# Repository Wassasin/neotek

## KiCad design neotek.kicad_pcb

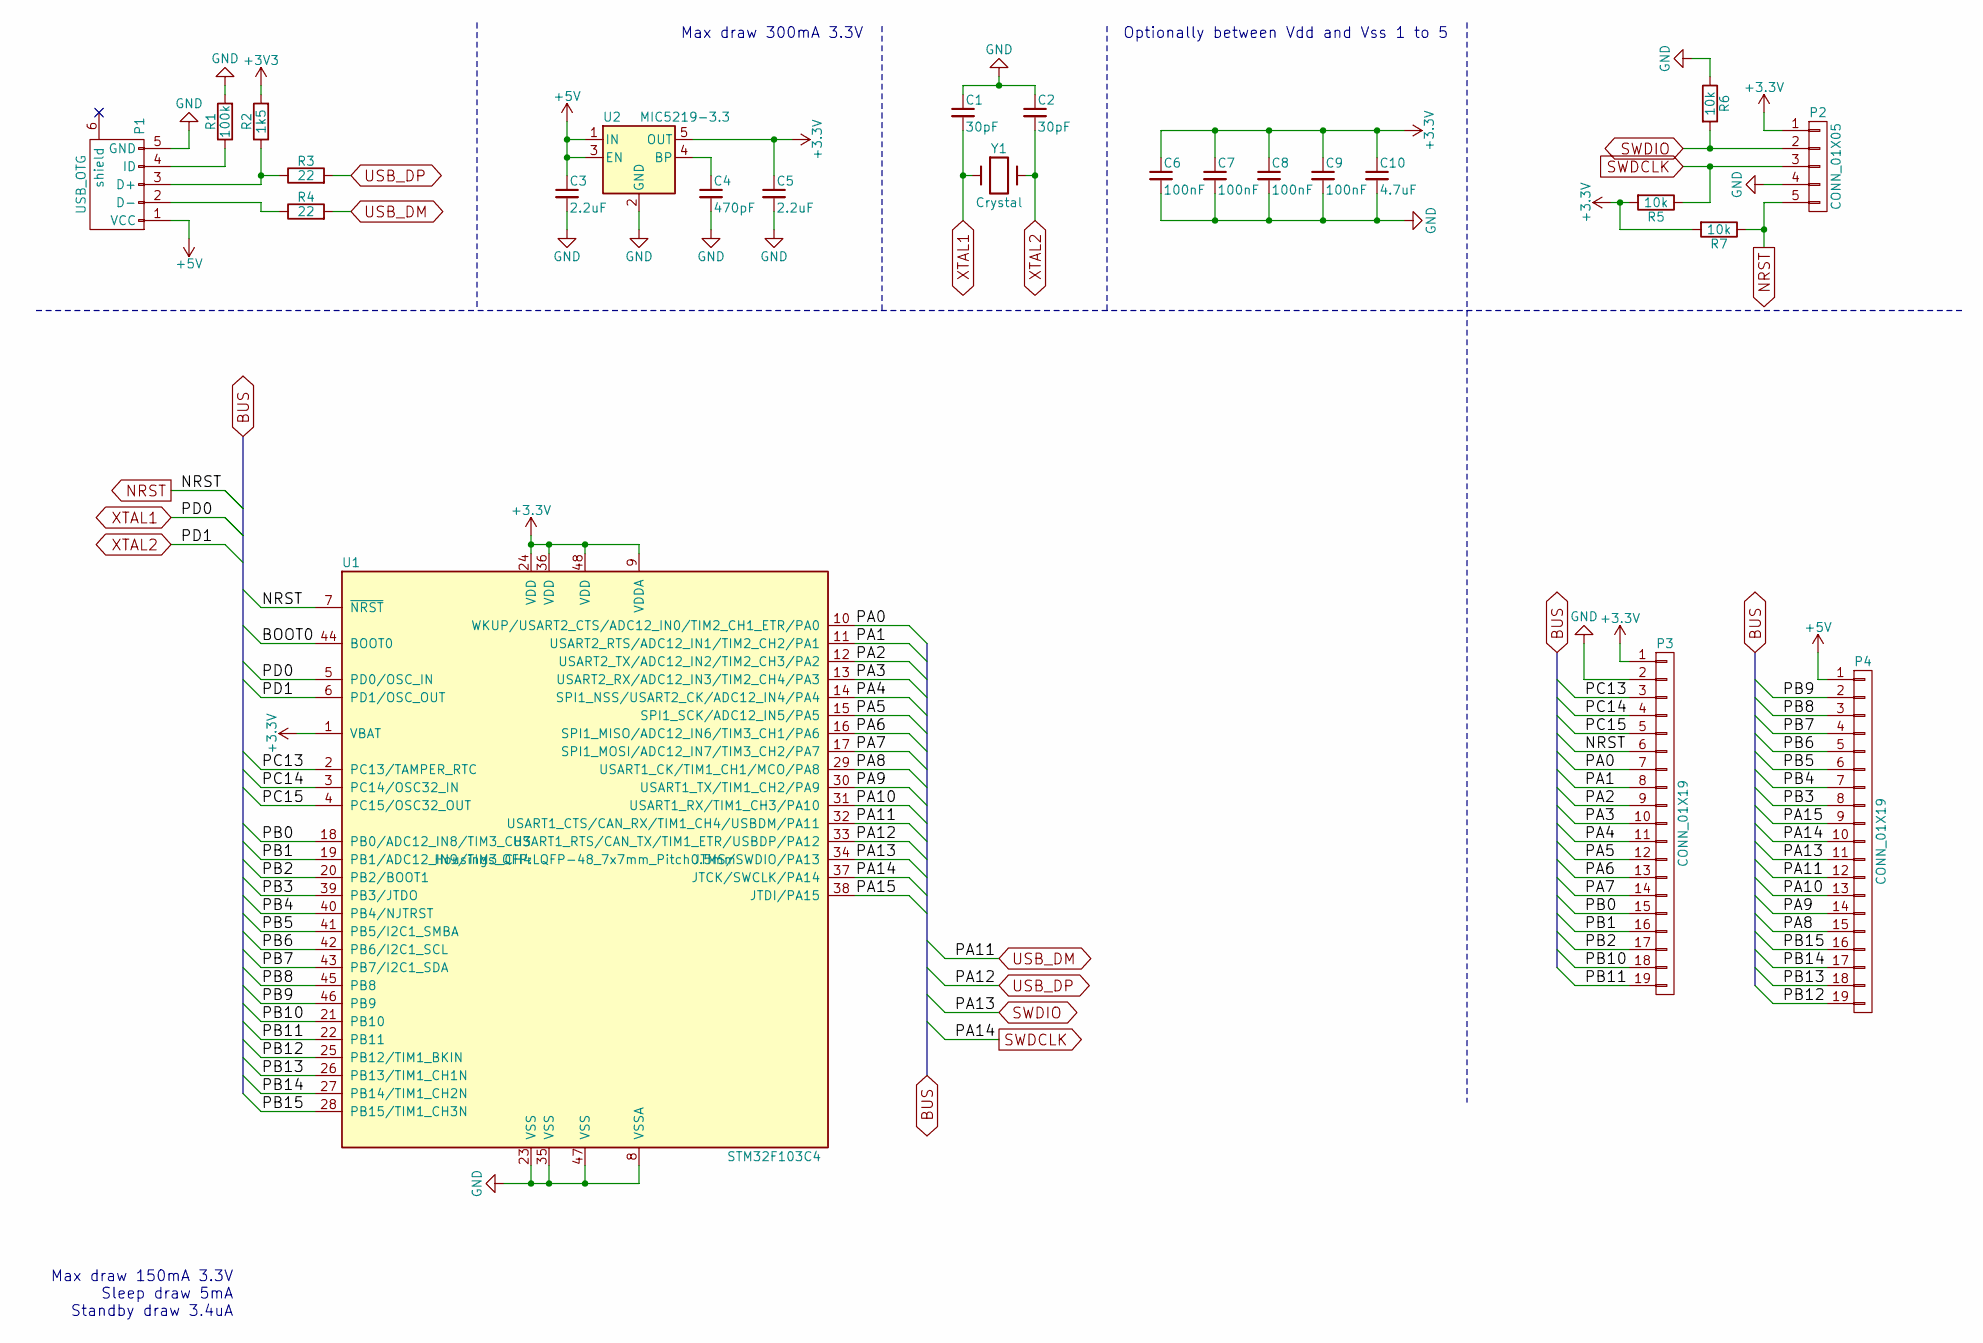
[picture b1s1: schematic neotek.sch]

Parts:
C1, C2: 30pF; C_0603_HandSoldering
C3, C5: 2.2uF; C_0603_HandSoldering
C4: 470pF; C_0603_HandSoldering
C6, C7, C8, C9: 100nF; C_0603_HandSoldering
C10: 4.7uF; C_0603_HandSoldering
P1: USB_OTG; USB_Micro-B_10103594-0001LF
P2: CONN_01X05; Hirose_DF13-05P-1.25DS_05x1.25mm_Angled
P3, P4: CONN_01X19; Pin_Header_Straight_1x19
R1: 100k; R_0603_HandSoldering
R2: 1k5; R_0603_HandSoldering
R3, R4: 22; R_0603_HandSoldering
R5, R6, R7: 10k; R_0603_HandSoldering
U1: STM32F103C4; LQFP-48_7x7mm_Pitch0.5mm
U2: MIC5219-3.3; SOT-23-5
Y1: Crystal; Crystal_HC49-SD_SMD

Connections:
+5V: C3.1, P1.1 (VCC), P4.1, U2.1 (IN), U2.3 (EN)
/BOOT0: U1.44 (BOOT0)
/PA0: P3.7, U1.10 (WKUP/USART2_CTS/ADC12_IN0/TIM2_CH1_ETR/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)
/PA1: P3.8, U1.11 (USART2_RTS/ADC12_IN1/TIM2_CH2/PA1)
/PA2: P3.9, U1.12 (USART2_TX/ADC12_IN2/TIM2_CH3/PA2)
/PA3: P3.10, U1.13 (USART2_RX/ADC12_IN3/TIM2_CH4/PA3)
/PA4: P3.11, U1.14 (SPI1_NSS/USART2_CK/ADC12_IN4/PA4)
/PA5: P3.12, U1.15 (SPI1_SCK/ADC12_IN5/PA5)
/PA6: P3.13, U1.16 (SPI1_MISO/ADC12_IN6/TIM3_CH1/PA6)
/PA7: P3.14, U1.17 (SPI1_MOSI/ADC12_IN7/TIM3_CH2/PA7)
/PA8: P4.15, U1.29 (USART1_CK/TIM1_CH1/MCO/PA8)
/PA9: P4.14, U1.30 (USART1_TX/TIM1_CH2/PA9)
/PA10: P4.13, U1.31 (USART1_RX/TIM1_CH3/PA10)
/PA15: P4.9, U1.38 (JTDI/PA15)
/PB0: P3.15, U1.18 (PB0/ADC12_IN8/TIM3_CH3)
/PB1: P3.16, U1.19 (PB1/ADC12_IN9/TIM3_CH4)
/PB2: P3.17, U1.20 (PB2/BOOT1)
/PB3: P4.8, U1.39 (PB3/JTDO)
/PB4: P4.7, U1.40 (PB4/NJTRST)
/PB5: P4.6, U1.41 (PB5/I2C1_SMBA)
/PB6: P4.5, U1.42 (PB6/I2C1_SCL)
/PB7: P4.4, U1.43 (PB7/I2C1_SDA)
/PB8: P4.3, U1.45 (PB8)
/PB9: P4.2, U1.46 (PB9)
/PB10: P3.18, U1.21 (PB10)
/PB11: P3.19, U1.22 (PB11)
/PB12: P4.19, U1.25 (PB12/TIM1_BKIN)
/PB13: P4.18, U1.26 (PB13/TIM1_CH1N)
/PB14: P4.17, U1.27 (PB14/TIM1_CH2N)
/PB15: P4.16, U1.28 (PB15/TIM1_CH3N)
/PC13: P3.3, U1.2 (PC13/TAMPER_RTC)
/PC14: P3.4, U1.3 (PC14/OSC32_IN)
/PC15: P3.5, U1.4 (PC15/OSC32_OUT)
GND: C1.1, C2.1, C3.2, C4.2, C5.2, C6.2, C7.2, C8.2, C9.2, C10.2, P1.5 (GND), P2.4, P3.2, R1.2, R6.1, U1.8 (VSSA), U1.23 (VSS), U1.35 (VSS), U1.47 (VSS), U2.2 (GND)
NRST: P2.5, P3.6, R7.1, U1.7 (~NRST)
unnamed: C4.1, U2.4 (BP)
unnamed: P1.2 (D-), R4.1
unnamed: P1.3 (D+), R2.1, R3.1
unnamed: P1.4 (ID), R1.1
SWDCLK: P2.3, P4.10, R5.1, U1.37 (JTCK/SWCLK/PA14)
SWDIO: P2.2, P4.11, R6.2, U1.34 (JTMS/SWDIO/PA13)
USB_DM: P4.12, R4.2, U1.32 (USART1_CTS/CAN_RX/TIM1_CH4/USBDM/PA11)
USB_DP: R3.2, U1.33 (USART1_RTS/CAN_TX/TIM1_ETR/USBDP/PA12)
XTAL1: C1.2, U1.5 (PD0/OSC_IN), Y1.1
XTAL2: C2.2, U1.6 (PD1/OSC_OUT), Y1.2

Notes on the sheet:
Max draw 300mA 3.3V
Max draw 150mA 3.3V Sleep draw 5mA Standby draw 3.4uA
Optionally between Vdd and Vss 1 to 5

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
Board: 2 copper layers, 24 parts (0 on the bottom side), 45 nets, no tracks yet.

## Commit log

2018-01-29 Added headers; made footprint & layout stub
